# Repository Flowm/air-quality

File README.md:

# Air Quality monitor
Implementation of an affordable indoor air quality monitor using various sensors connected to a microcontroller and streaming the data to a Raspberry Pi for analysis using [Node-RED](http://nodered.org/).

![Dashboard]

## Architecture

## Sensing Unit (air-sense)
In the sensing unit a [Teensy] microcontroller reads the sensor data from the connected sensors and sends it over the attached Bluetooth BLE module.

### Hardware
The following sensors are used:

#### Version 1
Original version with dedicated VOC MEMS sensor

| Category            | Name                 | Provides                             | Price |
|---------------------|----------------------|--------------------------------------|------:|
| Core                | [Teensy 3.2][Teensy] | Microcontroller                      |  ~24€ |
| Communication       | [HM-11]              | Bluethooth                           |   ~5€ |
| Sensors             | [BME280]             | Temperature, Pressure, Humidity      |  ~14€ |
| Sensors             | [iAQ-core C]         | VOC Sensor                           |  ~33€ |
|                     |                      | **Total**                            |  ~76€ |

#### Version 2
Updated version with recently released BME680 sensor

| Category            | Name                 | Provides                             | Price |
|---------------------|----------------------|--------------------------------------|------:|
| Core                | [Teensy 3.2][Teensy] | Microcontroller                      |  ~24€ |
| Communication       | [HM-11]              | Bluethooth                           |   ~5€ |
| Sensors             | [BME680]             | Temperature, Pressure, Humidity, VOC |  ~15€ |
|                     |                      | **Total**                            |  ~44€ |

#### Additional optional sensors
| Category            | Name                 | Provides                             | Price |
|---------------------|----------------------|--------------------------------------|------:|
| Sensors (optional)  | [MQ135]              | Analog Gas Sensor                    |   ~2€ |
| Sensors (optional)  | [SM-PWM-01C]         | Dust Sensor                          |  ~14€ |

### Wiring
A Fritzing sketch documenting the layout of the current hardware prototype is located in `air-sense/wiring`.

## Processing unit (air-pi)
This unit was installed and tested on a [Raspberry Pi 3], running Debian Jessie.
The purpose of this unit is to process all the data received via Bluetooth from the sensing unit and compute the current air quality index, based on the latest measurements.
This unit is also configured to display the current status, as well as triggering real-time notifications in case the air quality gets worse.

### Hardware
Besides the Raspberry Pi an additional Bluetooth BLE module is used to receive the data from wirelessly connected sensing units.

| Category       | Name                  | Price |
|----------------|-----------------------|------:|
| Core           | [Raspberry Pi 3]      | ~40€  |
| Comm           | [HM-11]               |  ~5€  |
| LED (optional) | [WS2812 RGB LED Ring] |  ~7€  |

The HM-11 BLE module is connected to the serial port of the Raspberry Pi:
- [TXD](http://pinout.xyz/pinout/pin8_gpio14)
- [RXD](http://pinout.xyz/pinout/pin10_gpio15)

The Neopixel LED ring can be additionally connected to the Raspberry Pi to indicate the current air quality directly on the processing unit.
- VCC (any)
- GND (any)
- [BCM 18](https://pinout.xyz/pinout/pin12_gpio18) (pin 12) for providing input to the LED

### Installation
Raspberry Pi 3 comes with a pre-installed version of Node-RED.
Additionally, the following node modules are used:
- [node-red-node-sqlite](https://www.npmjs.com/package/node-red-node-sqlite)
- [node-red-contrib-telegrambot](https://github.com/windkh/node-red-contrib-telegrambot)
- [node-red-dashboard](https://github.com/node-red/node-red-dashboard)
- [node-red-node-pi-neopixel](https://www.npmjs.com/package/node-red-node-pi-neopixel)
(for controlling the neopixel LEDs, an additional library needs to be installed. This can be done by following the instructions on the npmjs or github page of this module)

All the required flows needed for running the application can be found inside the `air-pi/node-red` folder.
These flows can be easily imported via the web-based GUI provided by Node-RED.

[Dashboard]: https://cloud.githubusercontent.com/assets/1117666/21831099/b9782bfa-d7a1-11e6-8d5f-f32e0b3c3636.png
[Teensy]: https://www.pjrc.com/teensy
[HM-11]: http://wiki.seeed.cc/Bluetooth_V4.0_HM_11_BLE_Module
[BME280]: https://www.bosch-sensortec.com/bst/products/all_products/bme280
[BME680]: https://www.bosch-sensortec.com/bst/products/all_products/bme680
[iAQ-core C]: http://ams.com/eng/Products/Environmental-Sensors/Air-Quality-Sensors/iAQ-core-C
[MQ135]: https://www.olimex.com/Products/Components/Sensors/SNS-MQ135
[SM-PWM-01C]: http://www.amphenol-sensors.com/en/component/edocman/3-co2/4-co2-modules/194-sm-pwm-01c
[Raspberry Pi 3]: https://www.raspberrypi.org/products/raspberry-pi-3-model-b
[WS2812 RGB LED Ring]: http://www.watterott.com/de/WS2812B-RGB-Ring-8

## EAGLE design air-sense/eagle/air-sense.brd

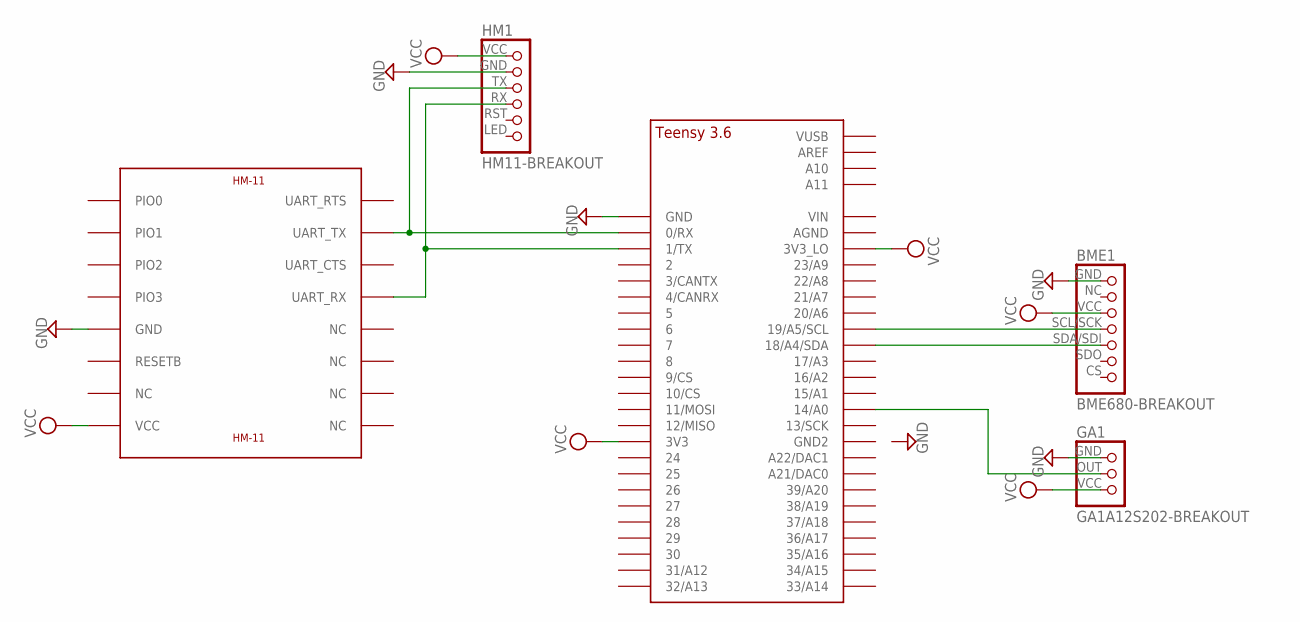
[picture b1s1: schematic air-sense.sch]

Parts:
BME1: BME680-BREAKOUT; BME680-1X07
GA1: GA1A12S202-BREAKOUT
HM1: HM11-BREAKOUT
U$1: TEENSY_3.5/3.6_BASIC
U$2: HM-11

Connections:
GND: BME1.GND, GA1.GND, HM1.GND, U$1.GND, U$2.GND
unnamed: HM1.TX, U$1.0/RX, U$2.UART_TX
unnamed: HM1.RX, U$1.1/TX, U$2.UART_RX
unnamed: GA1.OUT, U$1.14/A0
SCL: BME1.SCL/SCK, U$1.19/A5/SCL
SDA: BME1.SDA/SDI, U$1.18/A4/SDA
VCC: BME1.VCC, GA1.VCC, HM1.VCC, U$1.3V3, U$1.3V3_LO, U$2.VCC

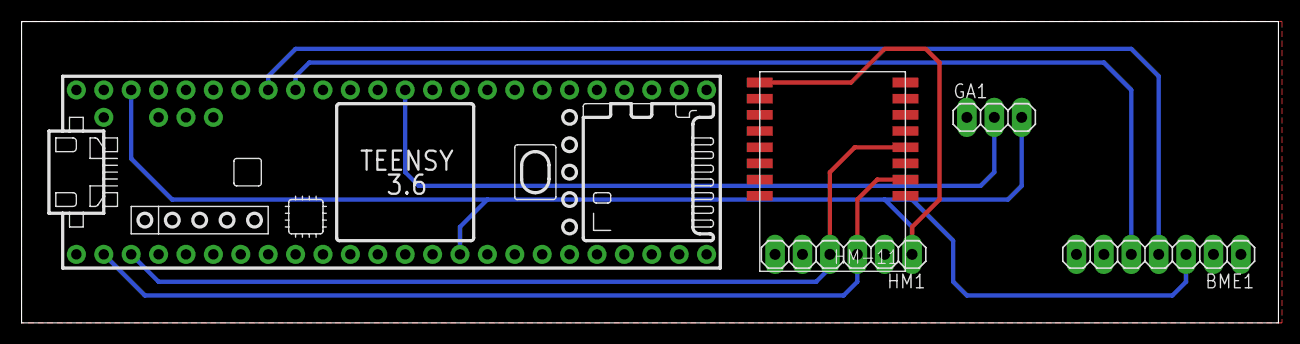
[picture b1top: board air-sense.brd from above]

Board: 2 copper layers, 116.5 x 27.9 mm, 5 parts (0 on the bottom side), 7 nets.

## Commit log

2016-11-21 Add simple sensor readout sketch
2016-11-21 Add some basic gnuplot data visualization
2016-11-28 Add node-red flow to parse sensor data from teensy
2016-12-06 Add basic node-red flow for telegram integration
2017-01-06 add Sensor analyzer flow
2017-01-06 adjust raw to json input mapping and filter input values
2017-01-06 Adjust sensor node data output format
2017-01-06 add filtering for iaq sensor data
2017-01-06 update sensor analysis with co2 and tvoc
2017-01-06 Use IAQ sensor for CO2 and TVOC measurement in sensor node
2017-01-07 Implement basic Dashboard to visualize sensor data
2017-01-08 Fix sensor values filtering
2017-01-08 update raw value analysis and add global function for that
2017-01-08 update dashboard labels and add raw humidex line
2017-01-09 Log sensor data over serial to BLE module and add minimal checksum
2017-01-09 update dashboard with highest value and fix card labels/sizes
2017-01-09 add checksum logic to received measurements (processing unit)
2017-01-09 ignore old measurements after some time and reset the value
2017-01-09 fix type of maximum value bug when joining values
2017-01-09 add ambient control flow
2017-01-09 sort elements in dashboard for color uniformity across charts
2017-01-10 Reduce amount of air quality notifications by only reporting relevant changes
2017-01-10 Change pin of MQ135 sensor for better position on breadboard
2017-01-10 Increase ambient controller light intensity again
2017-01-11 Add basic readme documenting the sensing unit
2017-01-11 add processing unit section to readme
2017-01-11 Include dashboard image in readme
2017-01-11 Use reference style links for cleaner tables in readme
2017-01-11 Document the wiring of the sensor unit with a fritzing sketch
2017-02-01 Document reduced processing unit hardware requirements
2017-02-01 Rename folders for monitor components and update documentation
2017-02-01 Basic implementation of SM-PWM-01C dust sensor module
2017-02-03 rpi-nodered: Update serial port and db path in SensorInput
2017-02-07 rpi-ansible: Store iaq measurements in sqlite db
2017-02-07 rpi-ansible: Filter irrelevant db values before sending
2017-04-14 sense-utils: Script to save serial output in sqlite db
2017-04-15 sense-utils: Workaround stdout buffer for more frequent db updates
2017-08-09 ser2mqtt: Basic mqtt connect
2017-08-09 ser2mqtt: Use mqtt loop and fix indention
2017-08-09 ser2mqtt: Read serial data line by line
2017-08-10 ser2mqtt: Convert serial data to json and publish it over mqtt
2017-08-10 ser2mqtt: Reduce amout of published messages
2017-08-10 ser2mqtt: Remove leading zeros for valid json
2017-08-11 ser2mqtt: Verify checksum to detect bluethooth transmission errors
2017-08-11 ser2mqtt: Ignore incomplete key value pairs
2017-08-11 ser2mqtt: Rely on checksum for verification instead of fixed key count
2017-08-11 ser2mqtt: Cleanup makefile and add install target
2017-10-08 rpi-ansible: Add ansible config as submodule after splitting it in a separate repository
2017-10-08 Add editorconfig
2017-10-08 Move data formatting to AQSensor
2017-10-08 Add analog gas and light sensor
2017-10-08 Cleanup iaq readout
2017-10-08 Fix indention
2017-10-08 Add support for the BME680 sensor
2017-10-09 Mention BME680 in readme
2017-10-10 Add air-sense v1 eagle files
2017-10-20 Add air-sense v2 eagle files with hm-11 pads
2017-10-22 Fix sensor data line endings
2017-10-29 Adjust functions for latest bme680 lib version
2017-10-29 Build format string incrementally
2017-10-29 Only add available sensor values
2017-10-30 Move sensor readout to AQSensor
2017-10-30 Disable usb serial by default
2017-10-30 Implement powersaving and disable usb serial by default
2017-10-30 Add required libs to documentation
2017-10-30 Disable mq135 analog gas sensor by default
2017-11-05 Update and fix checksum calculation
2017-11-05 Add ble data parsing on raspberry pi using bluepy
2017-11-05 Implement mqtt data publishing for full data sets
    Adjust callbacks and control flow
2017-11-05 Document required libraries for getting rpi ble module to work
2017-11-19 Only include Snooze lib when usb serial is disabled
2017-11-19 Fix string format buffer size
2017-12-03 Fix newline strip when parsing ble data
2017-12-03 Convert full dataset to json and publish sensors and dataset separately
2017-12-03 Cleanup code and parse int/float values separately
2017-12-03 Update documentation for air-ble and pip requirements
2017-12-03 Cleanup code and imports
2017-12-04 Handle disconnection error and attempt automatic reconnection
2017-12-04 Rename ble folder to ble2mqtt and add global gitignore file
2017-12-08 Fix syntax in requirements.txt
2017-12-08 Fix permissions for airpi_ble script
2017-12-08 Update piot-ansible submodule
2017-12-08 Add DS18B20 temperature sensor
2017-12-08 Rename AQSensor class
2017-12-08 Create wrapper class for BME680
2017-12-08 Improve DS18B20 wrapper class
2017-12-08 Create wrapper class for BME280
2017-12-08 Create wrapper class for analog sensors
2017-12-29 Add Bluefruit controller wrapper library for ble forwarding on feather m0 board
2018-01-04 Implement bluefruit variant in air-sense.ino logic
2018-02-03 Update arduino main with bluefruit defines and delay
2018-02-04 Replace escaped characters in data string with double escape in BluefruitController
2018-02-05 Fix sendData algorithm and enable ibeacon advertisement on bluefruit
2018-02-05 Move bluefruit configuration and perform initial operation within setup function
2018-02-05 Initialize output buffer in sendData function
2018-02-05 Only compile BluefruitController for Feather M0 target
2018-02-11 ser2mqtt: Fix readline EOL detection
2018-03-04 Set ble characterstic for bluefruit module (same uid as default hm-11 nordic chip is used)
2018-03-04 Use correct bluefruit characteristic inside air-sense main file
2018-05-27 Read from BME sensors only if correctly initialized, to avoid blocks
2018-05-27 Increase data parsing interval to 1 second
2018-10-14 Update ser2mqtt path in service file
2018-10-14 Add setup script for connector service
2018-10-14 Use https for submodule
2018-10-14 Add python ser2mqtt parser
2018-10-14 Move node red flows to the legacy folder
2018-10-14 Rename files
2018-10-14 Fix wrong class name in serial_aq_mqtt
2018-10-14 Cleanup MqttBroker
    Static client_id is not necessary: "If client_id is zero length or
    None, then one will be randomly generated"
2018-10-14 Move ser2mqtt files to lib folder
2018-10-14 Deprecate ser2mqtt c implementation
2018-10-14 Remove bluepy from connector requirements for now
